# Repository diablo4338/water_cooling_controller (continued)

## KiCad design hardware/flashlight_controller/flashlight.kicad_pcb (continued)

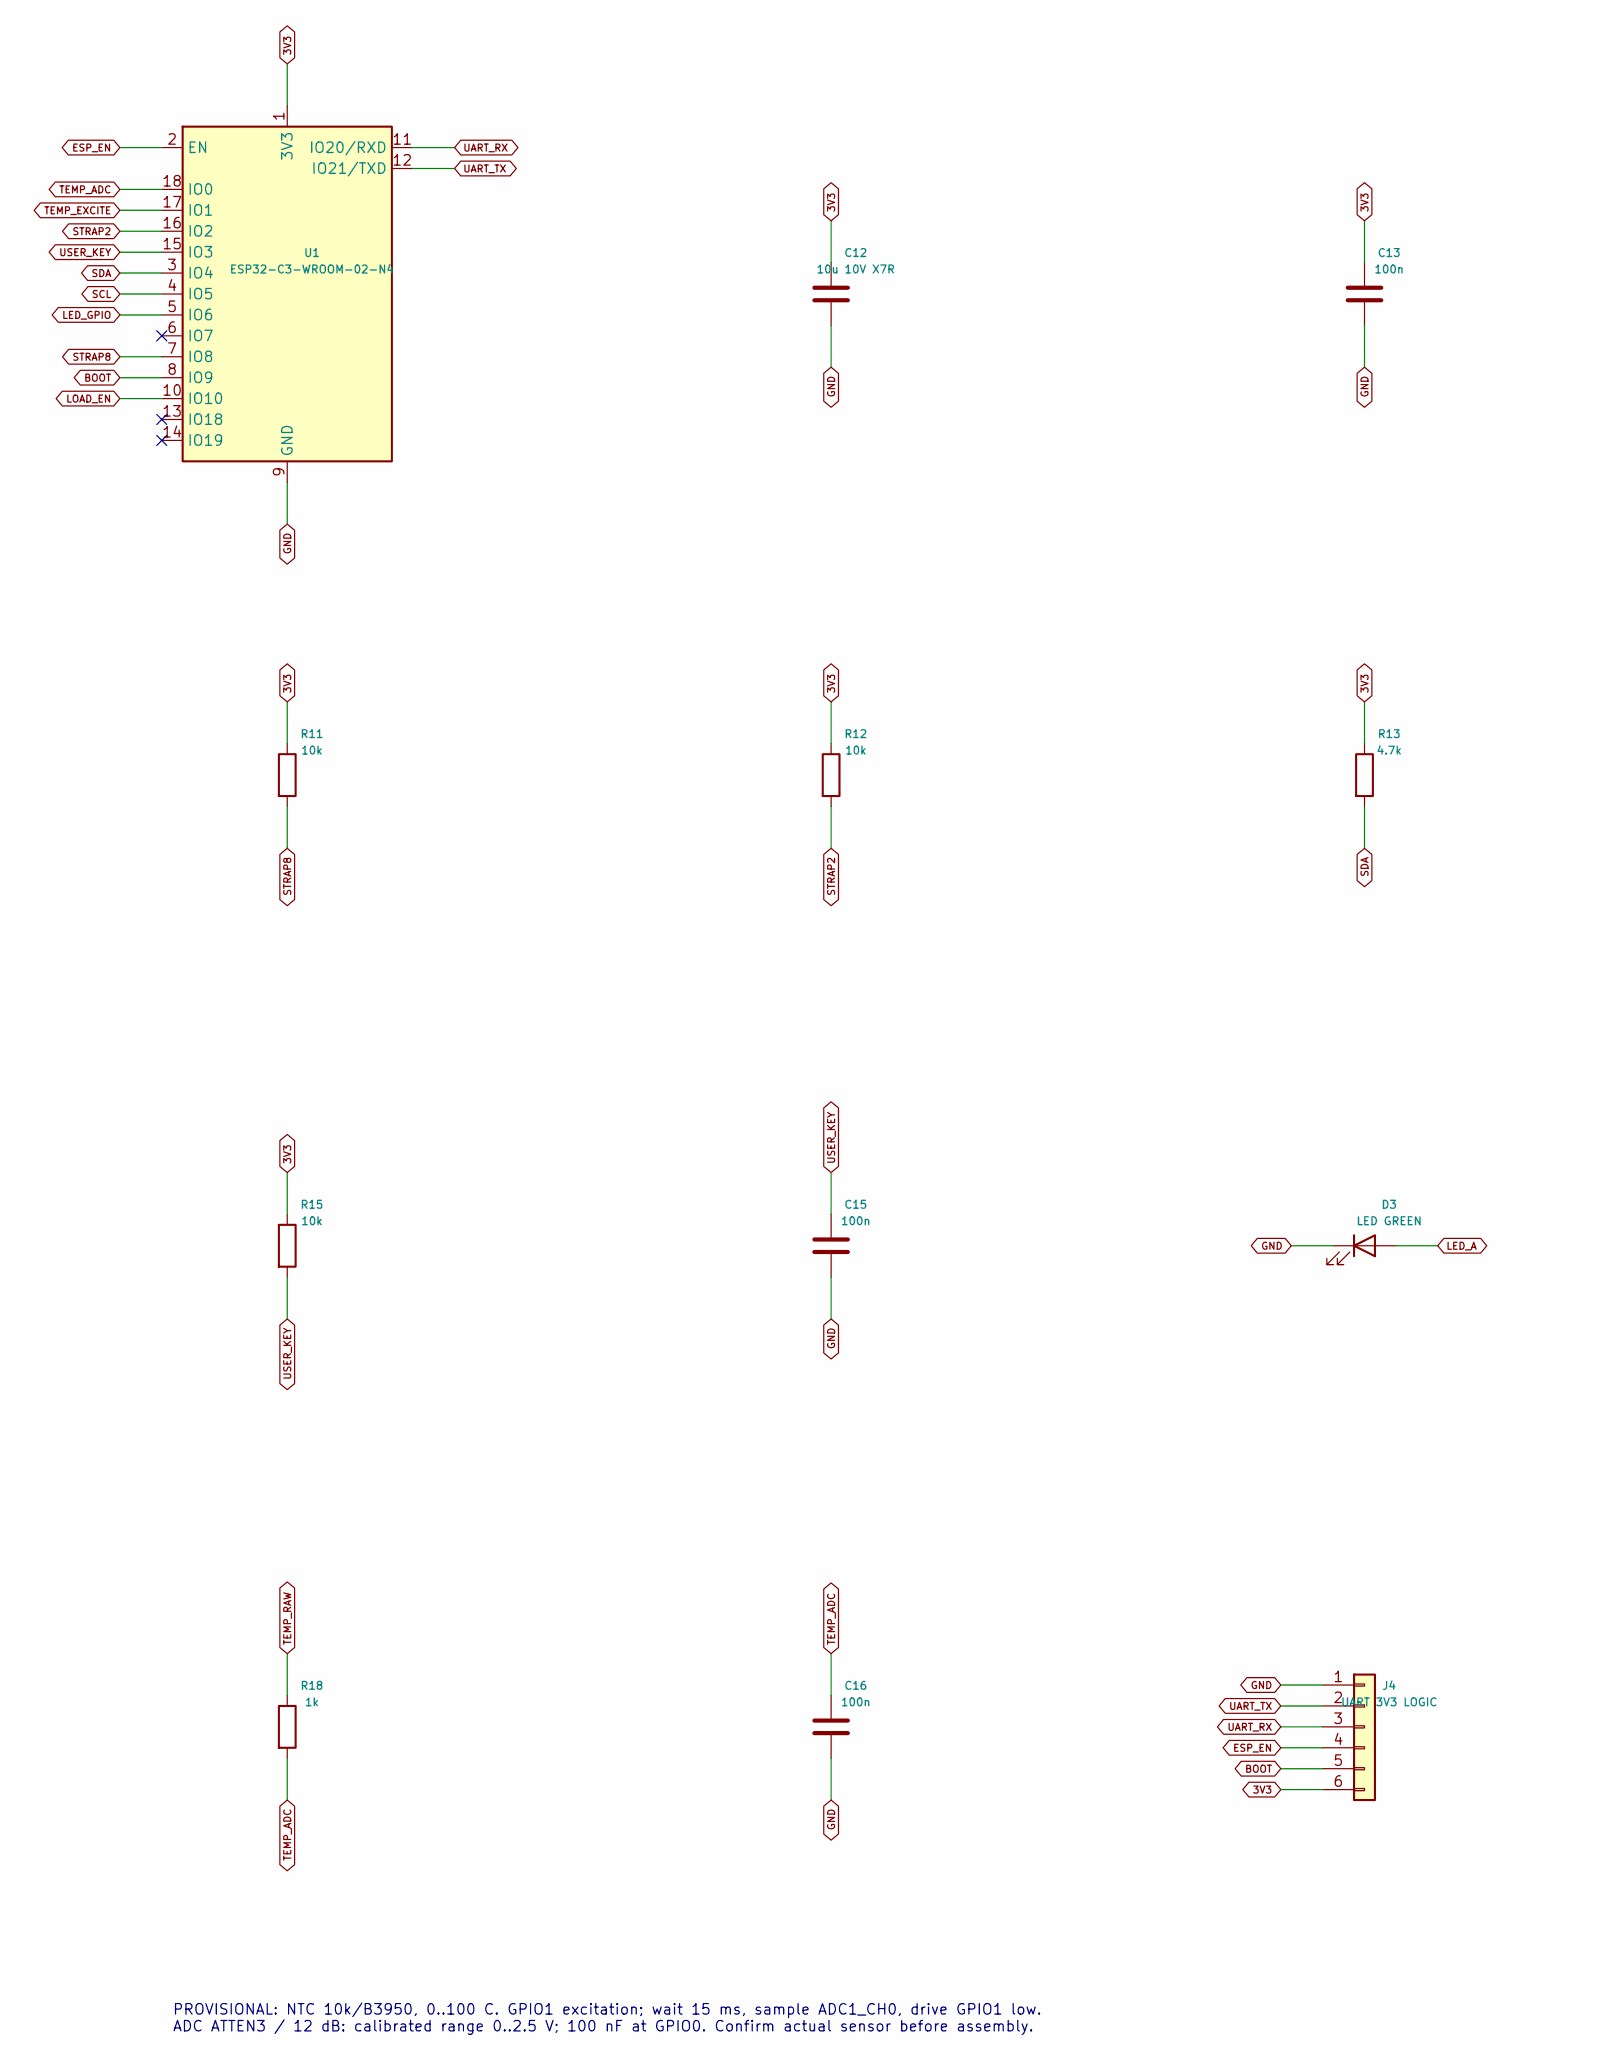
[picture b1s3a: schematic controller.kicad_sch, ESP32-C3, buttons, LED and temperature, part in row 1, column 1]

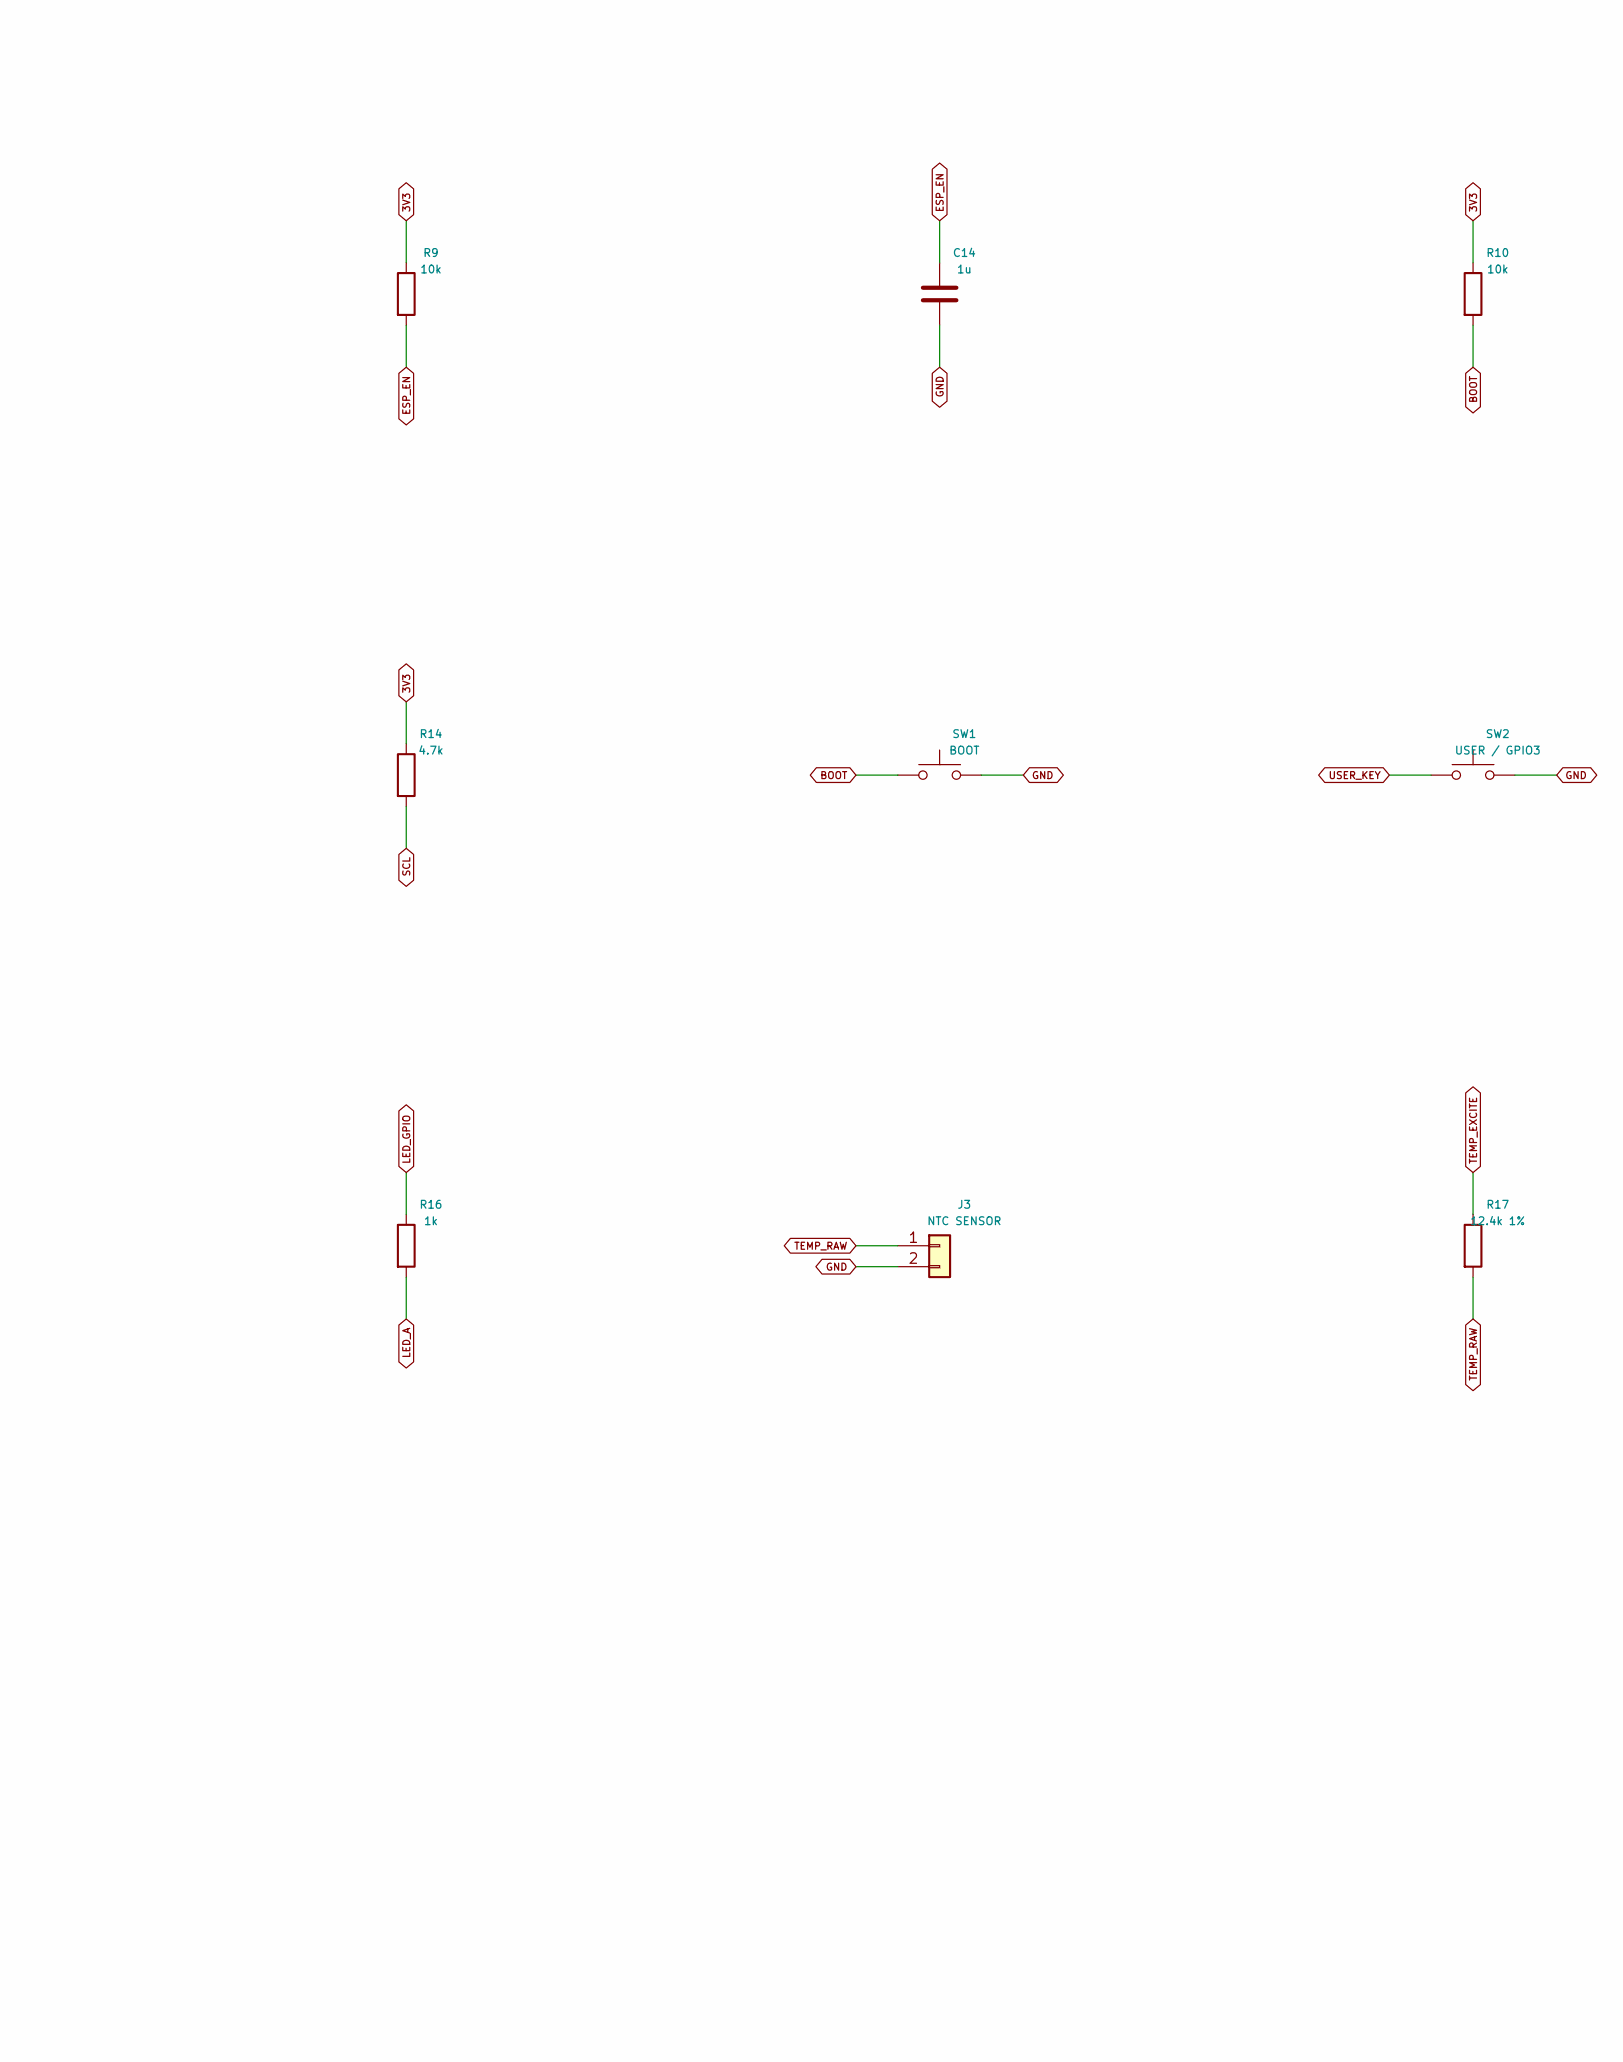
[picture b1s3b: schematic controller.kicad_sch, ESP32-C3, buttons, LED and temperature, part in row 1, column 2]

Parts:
C12: 10u 10V X7R; C_0805_2012Metric
C13, C15, C16: 100n; C_0805_2012Metric
C14: 1u; C_0805_2012Metric
D3: LED GREEN; LED_0805_2012Metric
J3: NTC SENSOR; SensorPads_2
J4: UART 3V3 LOGIC; UART_Pads_6
R9, R10, R11, R12, R15: 10k; R_0805_2012Metric
R13, R14: 4.7k; R_0805_2012Metric
R16, R18: 1k; R_0805_2012Metric
R17: 12.4k 1%; R_0805_2012Metric
SW1: BOOT; Reference_Button
SW2: USER / GPIO3; Reference_Button
U1: ESP32-C3-WROOM-02-N4; ESP32-C3-WROOM-02

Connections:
3V3: C12.1, C13.1, J4.6, R9.1, R10.1, R11.1, R12.1, R13.1, R14.1, R15.1, U1.1 (3V3); also elsewhere on the board
BOOT: J4.5, R10.2, SW1.1, U1.8 (IO9)
ESP_EN: C14.1, J4.4, R9.2, U1.2 (EN)
GND: C12.2, C13.2, C14.2, C15.2, C16.2, D3.1 (K), J3.2, J4.1, SW1.2, SW2.2, U1.9 (GND), U1.19 (GND); also elsewhere on the board
LED_A: D3.2 (A), R16.2
LED_GPIO: R16.1, U1.5 (IO6)
LOAD_EN: U1.10 (IO10); also elsewhere on the board
SCL: R14.2, U1.4 (IO5); also elsewhere on the board
SDA: R13.2, U1.3 (IO4); also elsewhere on the board
STRAP2: R12.2, U1.16 (IO2)
STRAP8: R11.2, U1.7 (IO8)
TEMP_ADC: C16.1, R18.2, U1.18 (IO0)
TEMP_EXCITE: R17.1, U1.17 (IO1)
TEMP_RAW: J3.1, R17.2, R18.1
UART_RX: J4.3, U1.11 (IO20/RXD)
UART_TX: J4.2, U1.12 (IO21/TXD)
USER_KEY: C15.1, R15.2, SW2.1, U1.15 (IO3)

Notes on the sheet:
PROVISIONAL: NTC 10k/B3950, 0..100 C. GPIO1 excitation; wait 15 ms, sample ADC1_CH0, drive GPIO1 low. ADC ATTEN3 / 12 dB: calibrated range 0..2.5 V; 100 nF at GPIO0. Confirm actual sensor before assembly.

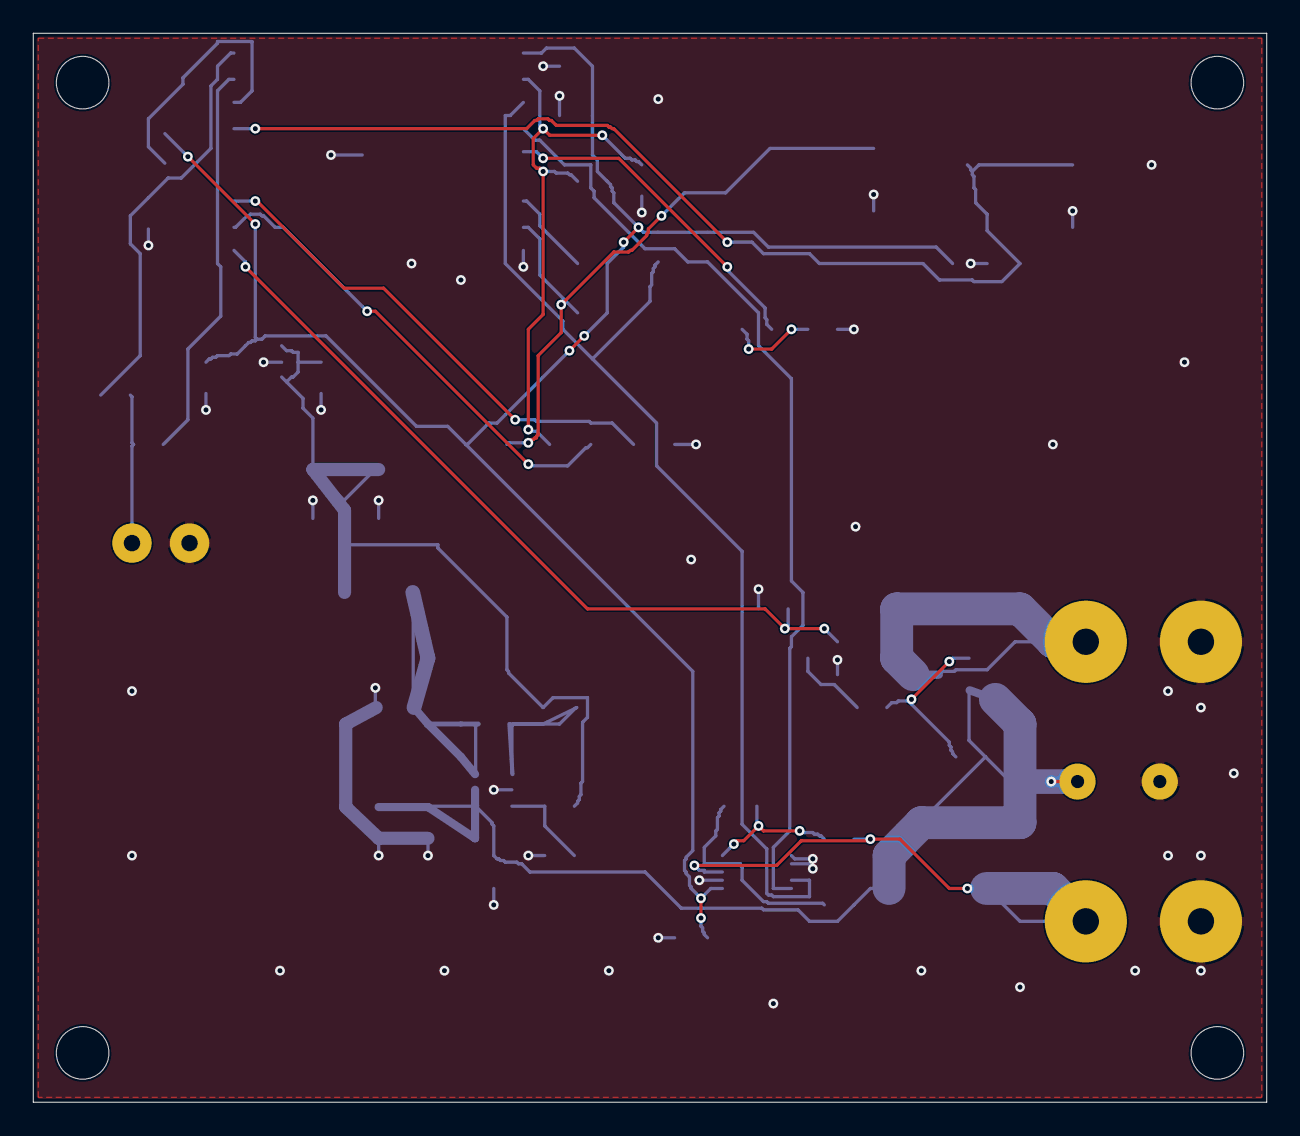
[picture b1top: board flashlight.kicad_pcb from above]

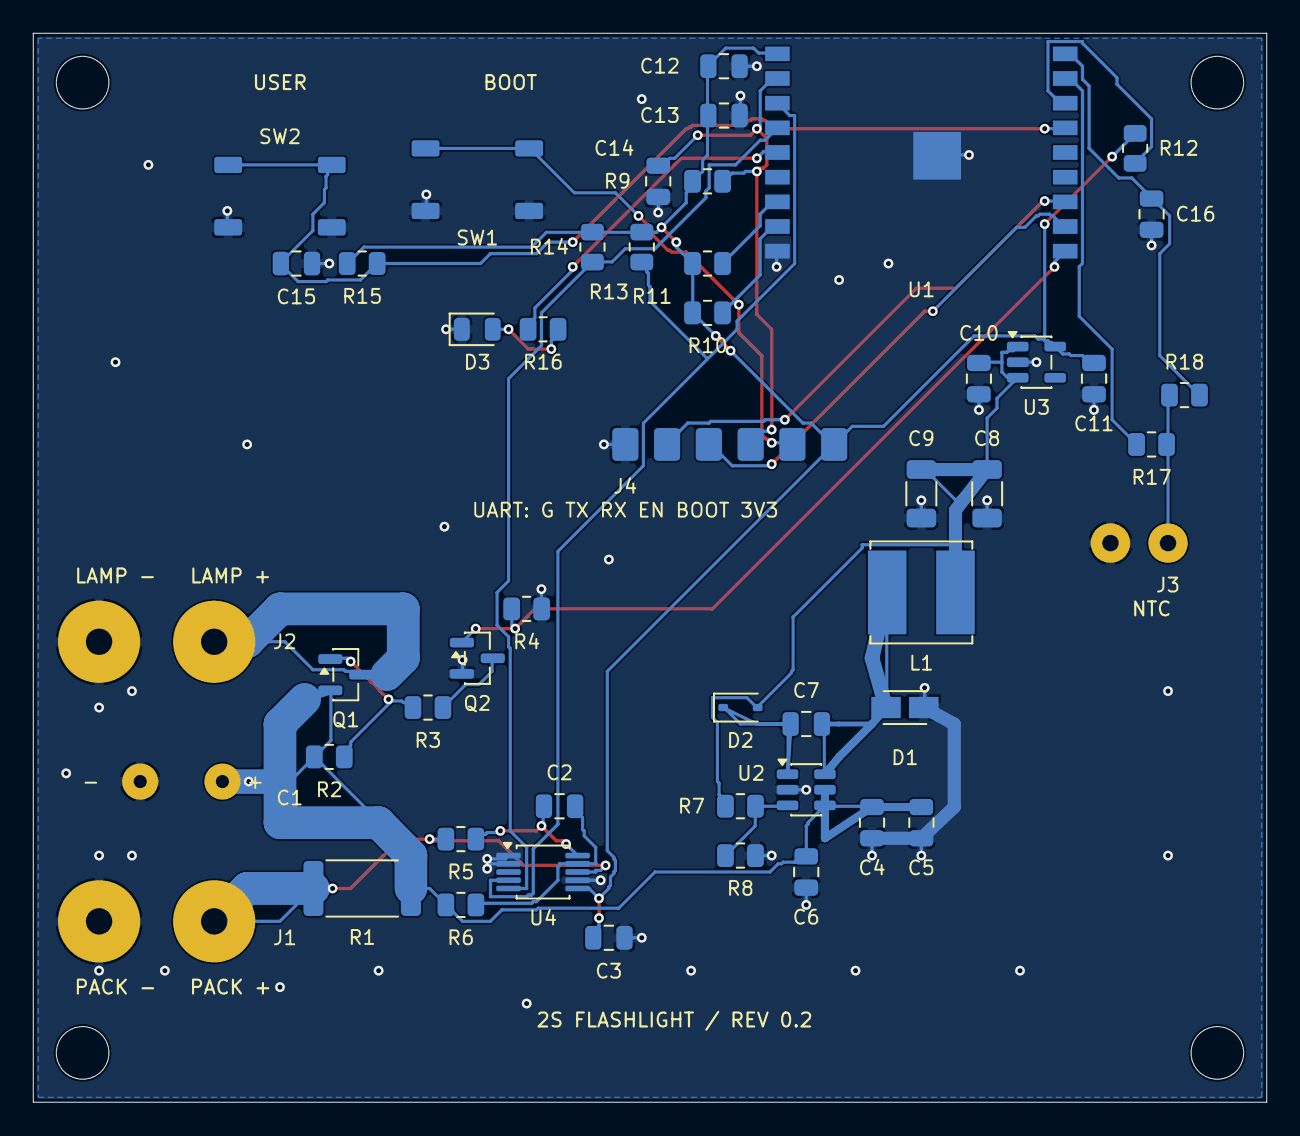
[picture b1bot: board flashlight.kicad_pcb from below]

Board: 2 copper layers, 75.0 x 65.0 mm, 54 parts (54 on the bottom side), 28 nets.

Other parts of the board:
H1, H2, H3, H4: MountingHole_3.2mm

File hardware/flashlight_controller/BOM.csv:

Reference,Value,Footprint,Notes
J1,PACK 2S / 6.0-8.4V,Flashlight:WirePads_2x_5mm,
J2,LAMP / 1A nominal,Flashlight:WirePads_2x_5mm,
R1,WSL2512R0470FEA,Flashlight:R_2512_6332Metric,Reference ina R17; 47mOhm 1% 1W; INA226 full scale 1.743A; update calibration
Q1,MMFTP3334K,Flashlight:SOT-23,"Reference fan_power Q1; verified G1 S2 D3; slow lamp on/off, not high-frequency PWM"
Q2,NXV40UNR,Flashlight:SOT-23,Reference fan_power Q2 / esp Q3; verified G1 S2 D3
R2,61.9k,Flashlight:R_0805_2012Metric,Reference 61k9; 11uA combined gate/sink leakage gives 0.681V off-state Vgs
R3,1k,Flashlight:R_0805_2012Metric,
R4,100k,Flashlight:R_0805_2012Metric,
C1,470u 16V low-ESR,Flashlight:Electrolytic_D10_P5,Bulk buffer for lamp pulses; mounted on bottom
U4,INA226AIDGSR,Flashlight:MSOP-10_3x3mm_P0.5mm,I2C address 0x40; VBUS senses raw pack voltage
R5,10R,Flashlight:R_0805_2012Metric,
R6,10R,Flashlight:R_0805_2012Metric,
C2,100n,Flashlight:C_0805_2012Metric,
C3,100n,Flashlight:C_0805_2012Metric,
U2,MCP16331T-E/CH,Flashlight:SOT-23-6,
C4,10u 16V X7R,Flashlight:C_0805_2012Metric,
C5,10u 16V X7R,Flashlight:C_0805_2012Metric,
C6,100n 16V,Flashlight:C_0805_2012Metric,
D1,PD3S120LQ,Flashlight:Reference_PowerDI323,"Reference fan_power D2; 20V 1A; cathode SW, anode GND"
L1,22uH / Isat>=1.2A,Flashlight:L_Bourns_SRN6045TA,SRN6045TA-220M or electrically equivalent footprint-compatible part
C7,100n 16V,Flashlight:C_0805_2012Metric,
D2,1N4148WS-HG3_A-08,Flashlight:D_SOD-323,"Reference fan_power D3; cathode BOOST, anode 5V"
C8,22u 10V X7R,Flashlight:C_1206_3216Metric,
C9,22u 10V X7R,Flashlight:C_1206_3216Metric,
R7,523k 1%,Flashlight:R_0805_2012Metric,Feedback current 8uA; verify stability on assembled board
R8,100k 1%,Flashlight:R_0805_2012Metric,"Reference 100k; practical design ceiling, no manufacturer maximum specified"
U3,TPS7A02-3.3,Flashlight:SOT-23-5,Reference power U2; TPS7A0233PDBVR; IN1 GND2 EN3 NC4 OUT5; rated 200mA
C10,1u 10V X7R,Flashlight:C_0805_2012Metric,Reference power C6; local LDO input bypass
C11,4.7u 10V X7R,Flashlight:C_0805_2012Metric,Reference power C5; local LDO output bypass
U1,ESP32-C3-WROOM-02-N4,Flashlight:ESP32-C3-WROOM-02,"GPIO0 ADC1_CH0, GPIO1 switched NTC excitation; antenna overhang ~6.5mm"
C12,10u 10V X7R,Flashlight:C_0805_2012Metric,
C13,100n,Flashlight:C_0805_2012Metric,
R9,10k,Flashlight:R_0805_2012Metric,
C14,1u,Flashlight:C_0805_2012Metric,
R10,10k,Flashlight:R_0805_2012Metric,
R11,10k,Flashlight:R_0805_2012Metric,
R12,10k,Flashlight:R_0805_2012Metric,
R13,4.7k,Flashlight:R_0805_2012Metric,
R14,4.7k,Flashlight:R_0805_2012Metric,
SW1,BOOT,Flashlight:Reference_Button,Reference esp button footprint
SW2,USER / GPIO3,Flashlight:Reference_Button,Reference esp button footprint
R15,10k,Flashlight:R_0805_2012Metric,
C15,100n,Flashlight:C_0805_2012Metric,
D3,LED GREEN,Flashlight:LED_0805_2012Metric,
R16,1k,Flashlight:R_0805_2012Metric,
J3,NTC SENSOR,Flashlight:SensorPads_2,"External NTC to ground; provisional 10k/B3950, confirm actual sensor"
R17,12.4k 1%,Flashlight:R_0805_2012Metric,Provisional NTC10k B3950 0..100C; GPIO1 high during sampling only; settle 15ms
R18,1k,Flashlight:R_0805_2012Metric,
C16,100n,Flashlight:C_0805_2012Metric,
J4,UART 3V3 LOGIC,Flashlight:UART_Pads_6,Pin 6 voltage reference only; power board from pack; boot hold + EN low pulse

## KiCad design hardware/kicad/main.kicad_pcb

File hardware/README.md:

# Hardware

Hardware assets for the controller: the KiCad board project, PCB production files, and the bill of materials.

## Structure
- `kicad/` - KiCad project sources:
  - `main.kicad_pro` - project file;
  - `main.kicad_sch` - top-level schematic;
  - `main.kicad_pcb` - PCB;
  - additional schematic sheets: `ads`, `esp`, `fan_power`, `fans`, `ina`, `power`.
- `production/gerbers/` - `Gerber` files for board fabrication.
- `production/drill/` - drill files.
- `production/bom/main.csv` - BOM.
- `production/schematic-pdf/main.pdf` - schematic PDF export.

## Production artifacts
[`../scripts/build_hardware.sh`](../scripts/build_hardware.sh) builds the following archive in `dist/`:

```text
pc-water-cooling-controller-<version>-hardware-gerbers-drill.zip
```

It contains:
- all files from `production/gerbers/`;
- all files from `production/drill/`.

The BOM is kept in the repository separately and is not packed by this script, so it should be treated as an independent manufacturing artifact.

## Practical use
If the task is related to board manufacturing or revision work, this directory contains the working inputs:
- source files for schematic and PCB changes;
- ready-to-send fabrication exports;
- the current component list.

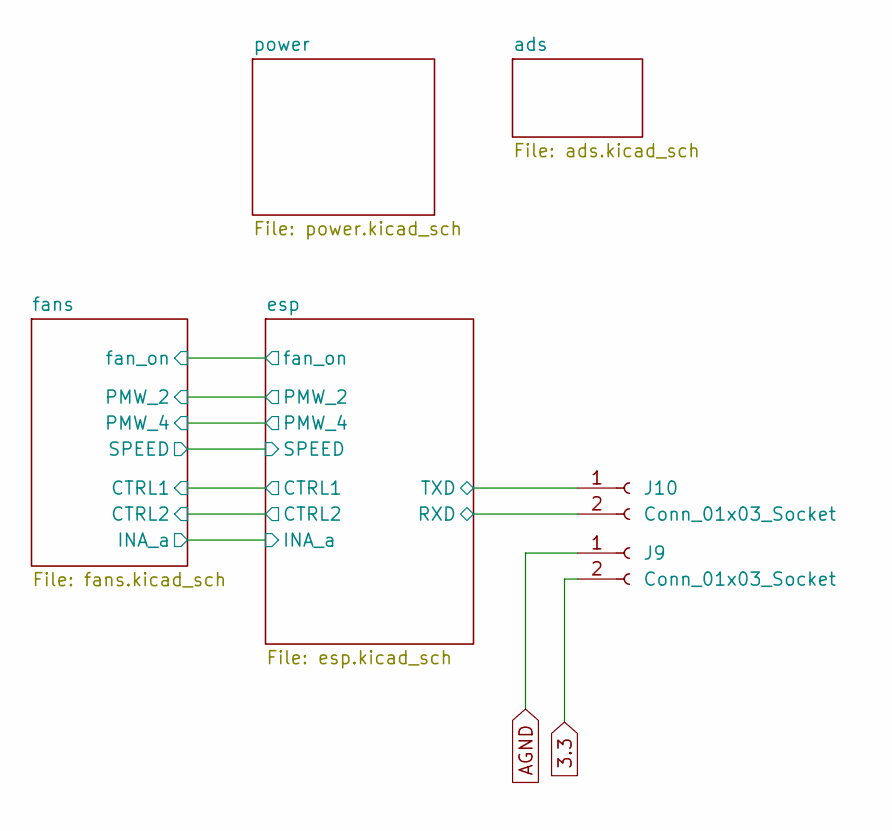
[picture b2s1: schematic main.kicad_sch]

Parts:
J9, J10: Conn_01x03_Socket; PinHeader_1x02_P2.54mm_Vertical

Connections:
3.3: J9.2; also elsewhere on the board
/esp/RXD: J10.2; also elsewhere on the board
/esp/TXD: J10.1; also elsewhere on the board
AGND: J9.1; also elsewhere on the board

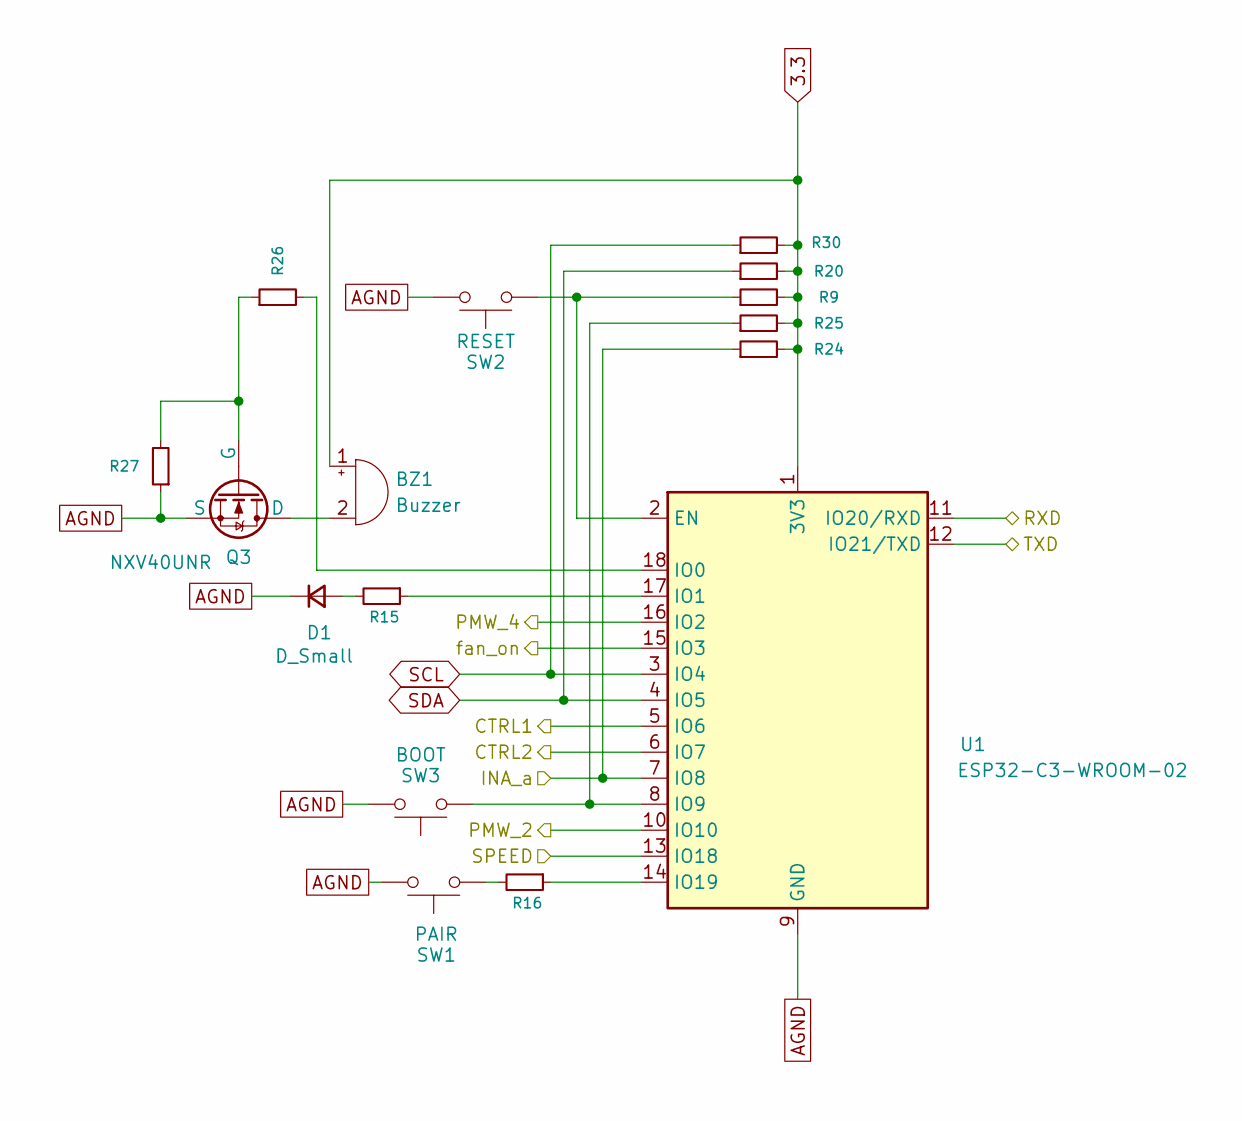
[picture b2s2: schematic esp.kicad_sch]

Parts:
BZ1: Buzzer; PinHeader_1x02_P2.54mm_Vertical
D1: D_Small; D_0805_2012Metric_Pad1.15x1.40mm_HandSolder
Q3: NXV40UNR; SOT-23-3
R9, R20, R24, R25, R30: 4k7; R_0805_2012Metric_Pad1.20x1.40mm_HandSolder
R15, R16: 1k; R_0805_2012Metric_Pad1.20x1.40mm_HandSolder
R26: 100; R_0805_2012Metric_Pad1.20x1.40mm_HandSolder
R27: 100k; R_0805_2012Metric_Pad1.20x1.40mm_HandSolder
SW1: PAIR; smd button
SW2: RESET; smd button
SW3: BOOT; smd button
U1: ESP32-C3-WROOM-02

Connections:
3.3: BZ1.1 (+), R9.2, R20.2, R24.2, R25.2, R30.2, U1.1 (3V3); also elsewhere on the board
/esp/CTRL1: U1.5 (IO6); also elsewhere on the board
/esp/CTRL2: U1.6 (IO7); also elsewhere on the board
/esp/INA_a: R24.1, U1.7 (IO8); also elsewhere on the board
/esp/PMW_2: U1.10 (IO10); also elsewhere on the board
/esp/PMW_4: U1.16 (IO2); also elsewhere on the board
/esp/RXD: U1.11 (IO20/RXD); also elsewhere on the board
/esp/SPEED: U1.13 (IO18); also elsewhere on the board
/esp/TXD: U1.12 (IO21/TXD); also elsewhere on the board
/esp/fan_on: U1.15 (IO3); also elsewhere on the board
AGND: D1.1 (K), Q3.2 (S), R27.1, SW1.2, SW2.2, SW3.2, U1.9 (GND), U1.19 (GND); also elsewhere on the board
unnamed: BZ1.2 (-), Q3.3 (D)
unnamed: D1.2 (A), R15.2
unnamed: Q3.1 (G), R26.1, R27.2
unnamed: R16.2, SW1.1
unnamed: R9.1, SW2.1, U1.2 (EN)
unnamed: R26.2, U1.18 (IO0)
unnamed: R15.1, U1.17 (IO1)
unnamed: R25.1, SW3.1, U1.8 (IO9)
unnamed: R16.1, U1.14 (IO19)
SCL: R30.1, U1.3 (IO4); also elsewhere on the board
SDA: R20.1, U1.4 (IO5); also elsewhere on the board

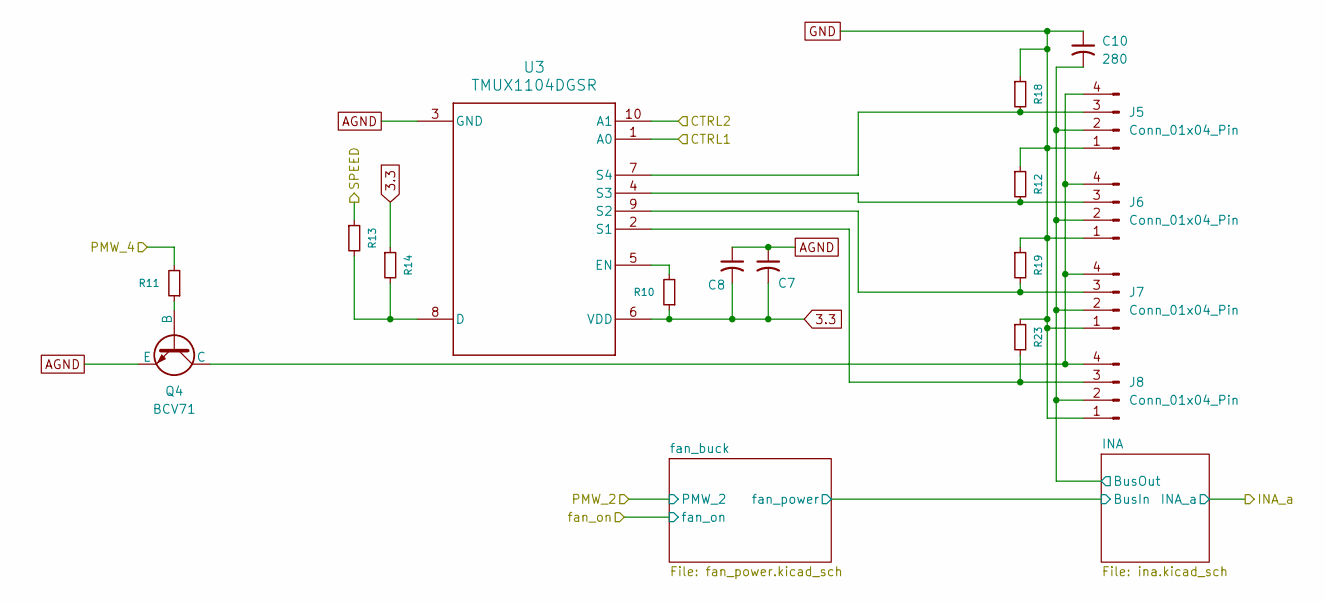
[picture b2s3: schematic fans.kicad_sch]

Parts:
C7: 1; C_0805_2012Metric_Pad1.18x1.45mm_HandSolder
C8: 0.1; C_0805_2012Metric_Pad1.18x1.45mm_HandSolder
C10: 280; CP_Radial_D8.0mm_P3.50mm
J5, J6, J7, J8: Conn_01x04_Pin; FanPinHeader_1x04_P2.54mm_Vertical
Q4: BCV71; SOT-23-3
R10, R12, R18, R19, R23: 100k; R_0805_2012Metric_Pad1.20x1.40mm_HandSolder
R11, R13: 2k2; R_0805_2012Metric_Pad1.20x1.40mm_HandSolder
R14: 4k7; R_0805_2012Metric_Pad1.20x1.40mm_HandSolder
U3: TMUX1104DGSR; DGS0010A-IPC_C

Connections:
3.3: C7.2, C8.2, R10.1, R14.1, U3.6 (VDD); also elsewhere on the board
/esp/CTRL1: U3.1 (A0); also elsewhere on the board
/esp/CTRL2: U3.10 (A1); also elsewhere on the board
/esp/PMW_4: R11.2; also elsewhere on the board
/esp/SPEED: R13.1; also elsewhere on the board
/fans/INA/BusOut: C10.2, J5.2 (VCC), J6.2 (VCC), J7.2 (VCC), J8.2 (VCC); also elsewhere on the board
AGND: C7.1, C8.1, Q4.2 (E), U3.3 (GND); also elsewhere on the board
GND: C10.1, J5.1 (GND), J6.1 (GND), J7.1 (GND), J8.1 (GND), R12.1, R18.1, R19.1, R23.1; also elsewhere on the board
unnamed: J5.4 (PMW), J6.4 (PMW), J7.4 (PMW), J8.4 (PMW), Q4.3 (C)
unnamed: J5.3 (TAHO), R18.2, U3.7 (S4)
unnamed: J6.3 (TAHO), R12.2, U3.4 (S3)
unnamed: J7.3 (TAHO), R19.2, U3.9 (S2)
unnamed: J8.3 (TAHO), R23.2, U3.2 (S1)
unnamed: Q4.1 (B), R11.1
unnamed: R13.2, R14.2, U3.8 (D)
unnamed: R10.2, U3.5 (EN)

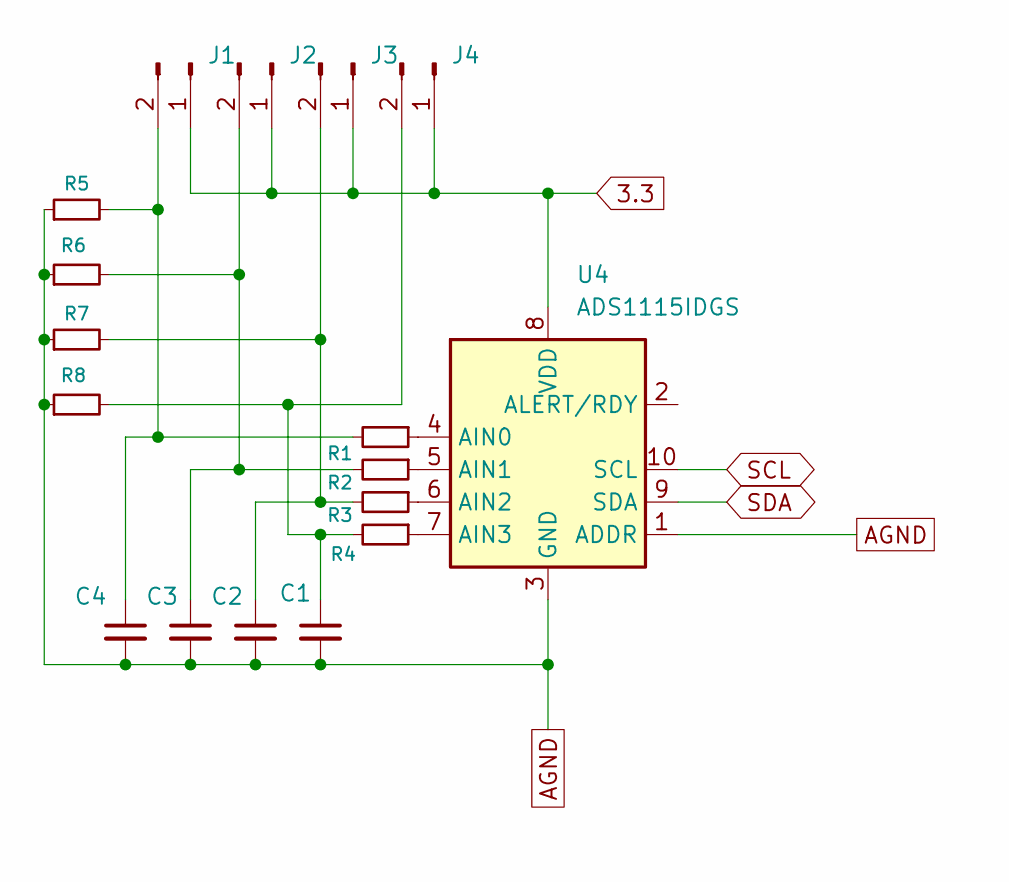
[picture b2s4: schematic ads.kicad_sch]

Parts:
C1, C2, C3, C4: 0.1; C_0805_2012Metric_Pad1.18x1.45mm_HandSolder
J1, J2, J3, J4: Conn_01x02_Pin; PinHeader_1x02_P2.54mm_Horizontal
R1, R2, R3, R4: 330; R_0805_2012Metric_Pad1.20x1.40mm_HandSolder
R5, R6, R7, R8: 4k7; R_0805_2012Metric_Pad1.20x1.40mm_HandSolder
U4: ADS1115IDGS; DGS0010A_N

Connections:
3.3: J1.1, J2.1, J3.1, J4.1, U4.8 (VDD); also elsewhere on the board
AGND: C1.2, C2.2, C3.2, C4.2, R5.1, R6.1, R7.1, R8.1, U4.1 (ADDR), U4.3 (GND); also elsewhere on the board
unnamed: C4.1, J1.2, R1.2, R5.2
unnamed: C3.1, J2.2, R2.2, R6.2
unnamed: C2.1, J3.2, R3.2, R7.2
unnamed: C1.1, J4.2, R4.2, R8.2
unnamed: R1.1, U4.4 (AIN0)
unnamed: R2.1, U4.5 (AIN1)
unnamed: R3.1, U4.6 (AIN2)
unnamed: R4.1, U4.7 (AIN3)
SCL: U4.10 (SCL); also elsewhere on the board
SDA: U4.9 (SDA); also elsewhere on the board

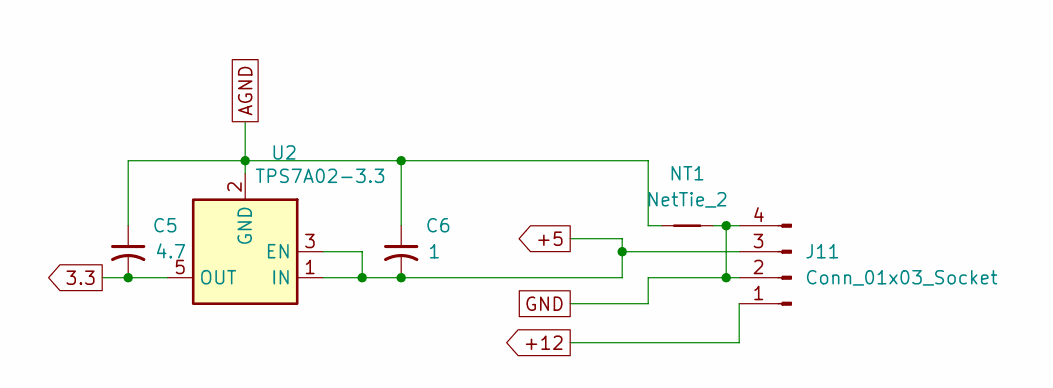
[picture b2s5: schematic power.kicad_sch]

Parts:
C5: 4.7; C_0805_2012Metric_Pad1.18x1.45mm_HandSolder
C6: 1; C_0805_2012Metric_Pad1.18x1.45mm_HandSolder
J11: Conn_01x03_Socket; sata
NT1: NetTie_2; NetTie-2_SMD_Pad0.5mm
U2: TPS7A02-3.3; SOT-23-5

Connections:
3.3: C5.2, U2.5 (OUT); also elsewhere on the board
+5: C6.2, J11.3 (+5), U2.1 (IN), U2.3 (EN); also elsewhere on the board
+12: J11.1 (+12); also elsewhere on the board
AGND: C5.1, C6.1, NT1.1, U2.2 (GND); also elsewhere on the board
GND: J11.2 (GND), J11.4 (AGND), NT1.2; also elsewhere on the board

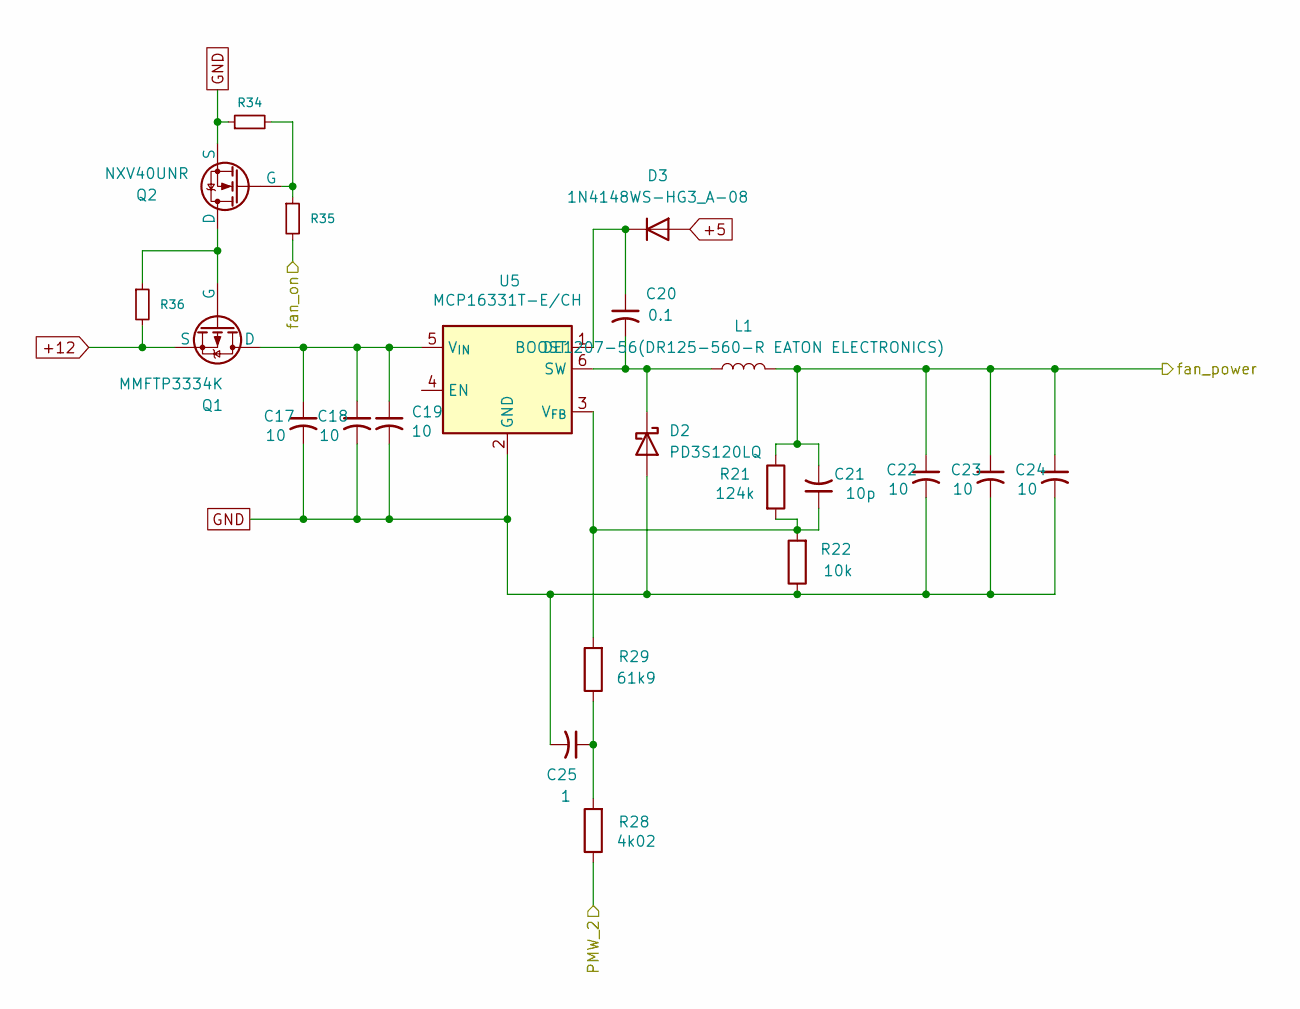
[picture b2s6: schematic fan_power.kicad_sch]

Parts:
C17, C18, C19, C22, C23, C24: 10; C_0805_2012Metric_Pad1.18x1.45mm_HandSolder
C20: 0.1; C_0805_2012Metric_Pad1.18x1.45mm_HandSolder
C21: 10p; C_0805_2012Metric_Pad1.18x1.45mm_HandSolder
C25: 1; C_0805_2012Metric_Pad1.18x1.45mm_HandSolder
D2: PD3S120LQ; 323_2
D3: 1N4148WS-HG3_A-08; D_SOD-323_HandSoldering
L1: DE1207-56(DR125-560-R EATON ELECTRONICS); SRN4018
Q1: MMFTP3334K; SOT-23-3
Q2: NXV40UNR; SOT-23-3
R21: 124k; R_0805_2012Metric_Pad1.20x1.40mm_HandSolder
R22: 10k; R_0805_2012Metric_Pad1.20x1.40mm_HandSolder
R28: 4k02; R_0805_2012Metric_Pad1.20x1.40mm_HandSolder
R29: 61k9; R_0805_2012Metric_Pad1.20x1.40mm_HandSolder
R34, R36: 100k; R_0805_2012Metric_Pad1.20x1.40mm_HandSolder
R35: 100; R_0805_2012Metric_Pad1.20x1.40mm_HandSolder
U5: MCP16331T-E/CH; SOT-23-6

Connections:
+5: D3.2 (A); also elsewhere on the board
+12: Q1.2 (S), R36.2; also elsewhere on the board
/esp/PMW_2: R28.1; also elsewhere on the board
/esp/fan_on: R35.2; also elsewhere on the board
/fans/INA/BusIn: C21.2, C22.1, C23.1, C24.1, L1.2, R21.1; also elsewhere on the board
GND: C17.2, C18.2, C19.2, C22.2, C23.2, C24.2, C25.2, D2.2 (A), Q2.2 (S), R22.1, R34.1, U5.2 (GND); also elsewhere on the board
unnamed: C25.1, R28.2, R29.1
unnamed: C20.2, D2.1 (K), L1.1, U5.6 (SW)
unnamed: C20.1, D3.1 (K), U5.1 (BOOST)
unnamed: C17.1, C18.1, C19.1, Q1.3 (D), U5.5 (V_{IN})
unnamed: Q1.1 (G), Q2.3 (D), R36.1
unnamed: Q2.1 (G), R34.2, R35.1
unnamed: C21.1, R21.2, R22.2, R29.2, U5.3 (V_{FB})
